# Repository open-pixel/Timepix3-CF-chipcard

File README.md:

# Timepix3-CF-chipcard
A compact Open Hardware chipboard for the Timepix3 chip from the [Medipix Collaboration](https://medipix.web.cern.ch/home) reusing the CompactFlash form factor.

Open the project file `TPX3_CF_chipcard.kicad_pro` in [KiCad V5.99 (*nightly version*)](https://www.kicad.org/download/) or the future version V6 once it is released. 

This project is licensed uner the CERN Open Hardware License: [CERN-OHL-P v2](LICENSE)

#### TODO:
- add more description and images
- 3D custom model files for the card enclosure and KiCad renderings
- update schematic with part order numbers

Author:
[Oliver Keller](https://www.github.com/ozel) (CERN/University of Geneva) 2021

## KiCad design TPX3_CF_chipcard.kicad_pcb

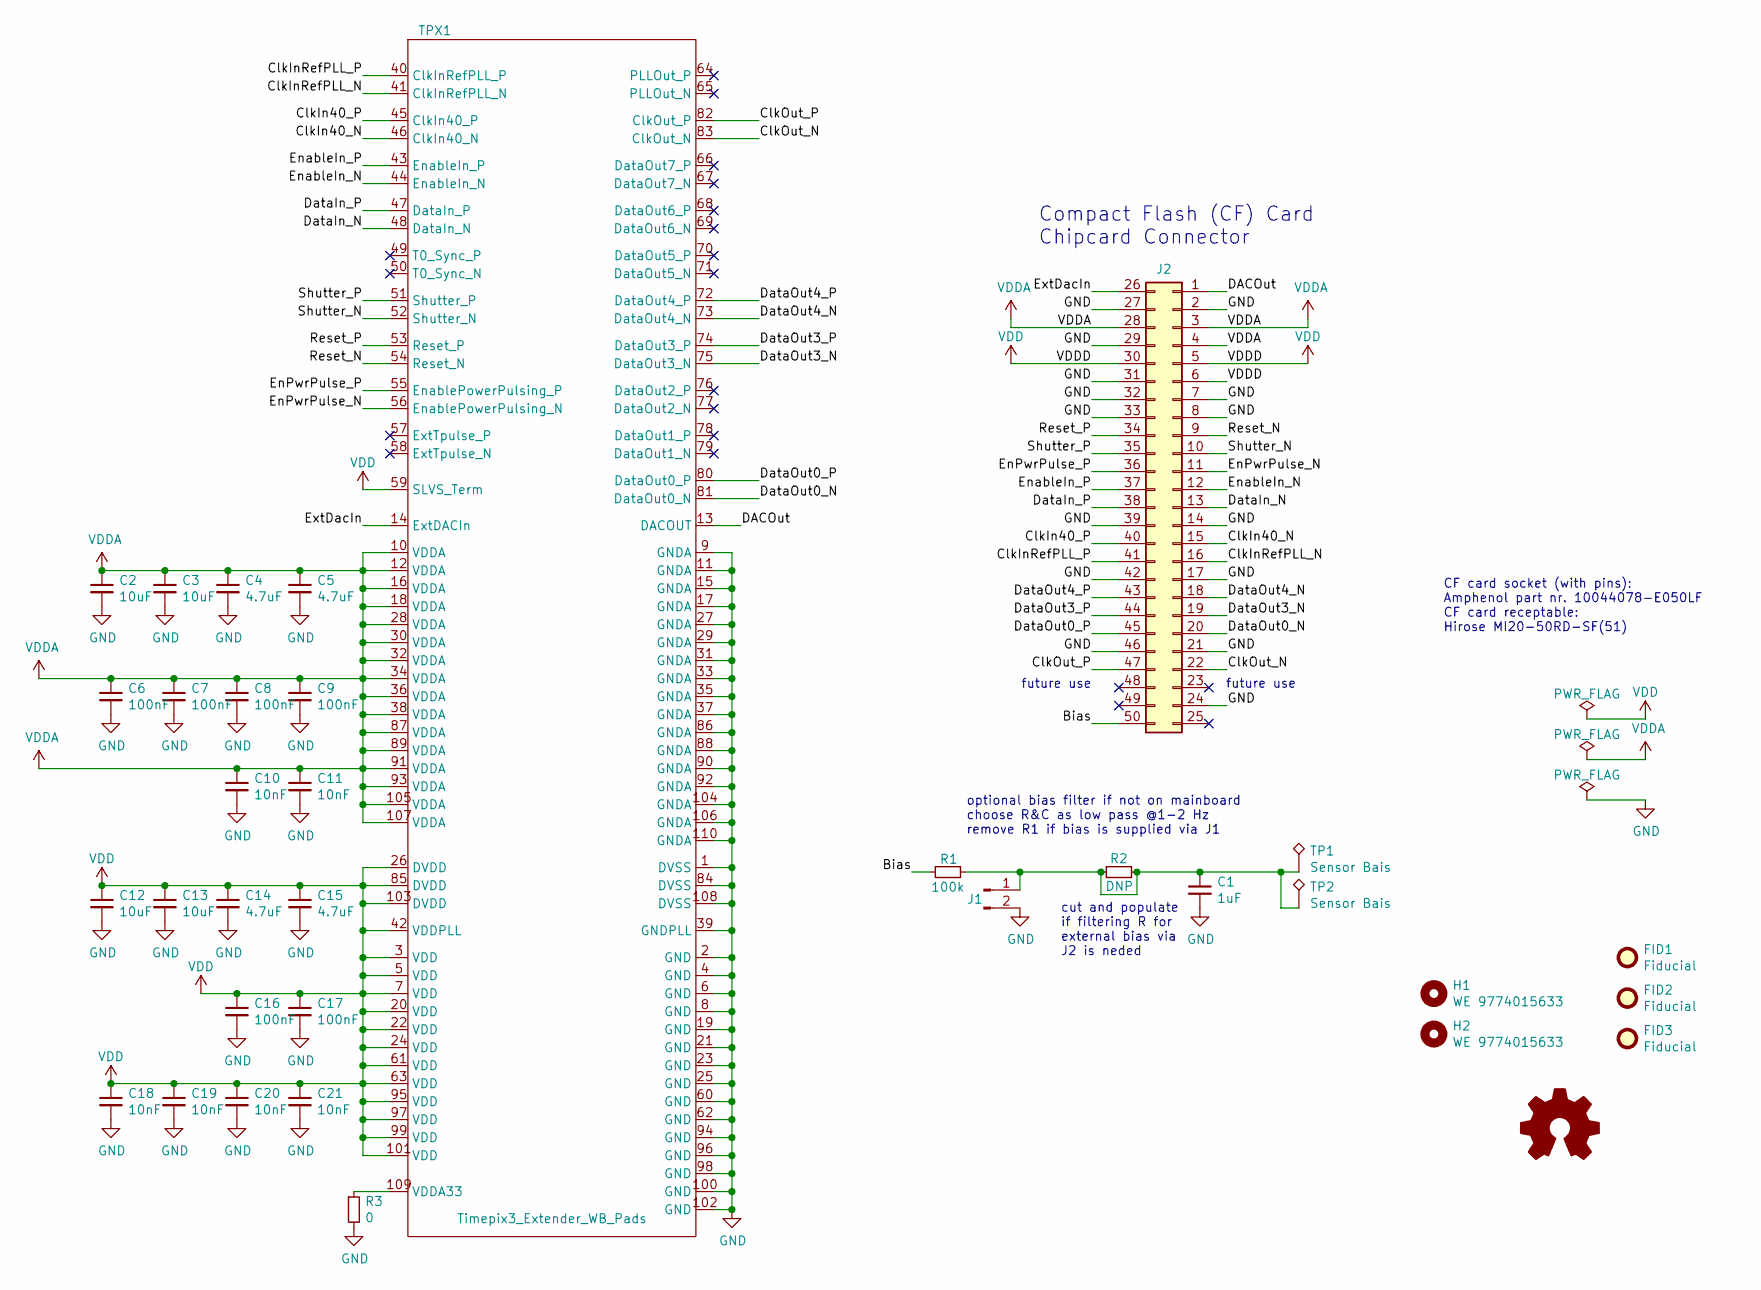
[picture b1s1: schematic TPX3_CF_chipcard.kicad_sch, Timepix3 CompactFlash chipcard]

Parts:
C1: 1uF; C_0805_2012Metric
C2, C3, C12, C13: 10uF; C_1206_3216Metric
C4, C5, C14, C15: 4.7uF; C_0805_2012Metric
C6, C7, C8, C9, C16, C17: 100nF; C_0402_1005Metric
C10, C11, C18, C19, C20, C21: 10nF; C_0402_1005Metric
FID1, FID2, FID3: Fiducial; Fiducial_0.75mm_Mask1.5mm
H1, H2: WE 9774015633; MountingHole_2.1mm
J1: Conn_01x02_Male; PinHeader_1x02_P2.54mm_Vertical
J2: MI20-50RD-SF(51); CF-Card_Hirose_MI20-50RD-SF(51)
LOGO1: Logo_Open_Hardware_Small; OSHW-Symbol_6.7x6mm_Copper
R1: 100k; R_0603_1608Metric
R2: DNP; R_0603_1608Metric
R3: 0; R_0603_1608Metric
TP1, TP2: Sensor Bais; TestPoint_Pad_2.0x2.0mm
TPX1: Timepix3_Extender_WB_Pads; Timepix3_lowcostWBpads

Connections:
/Bias: J2.50, R1.2
/ClkIn40_N: J2.15, TPX1.46 (ClkIn40_N)
/ClkIn40_P: J2.40, TPX1.45 (ClkIn40_P)
/ClkInRefPLL_N: J2.16, TPX1.41 (ClkInRefPLL_N)
/ClkInRefPLL_P: J2.41, TPX1.40 (ClkInRefPLL_P)
/ClkOut_N: J2.22, TPX1.83 (ClkOut_N)
/ClkOut_P: J2.47, TPX1.82 (ClkOut_P)
/DACOut: J2.1, TPX1.13 (DACOUT)
/DataIn_N: J2.13, TPX1.48 (DataIn_N)
/DataIn_P: J2.38, TPX1.47 (DataIn_P)
/DataOut0_N: J2.20, TPX1.81 (DataOut0_N)
/DataOut0_P: J2.45, TPX1.80 (DataOut0_P)
/DataOut3_N: J2.19, TPX1.75 (DataOut3_N)
/DataOut3_P: J2.44, TPX1.74 (DataOut3_P)
/DataOut4_N: J2.18, TPX1.73 (DataOut4_N)
/DataOut4_P: J2.43, TPX1.72 (DataOut4_P)
/EnPwrPulse_N: J2.11, TPX1.56 (EnablePowerPulsing_N)
/EnPwrPulse_P: J2.36, TPX1.55 (EnablePowerPulsing_P)
/EnableIn_N: J2.12, TPX1.44 (EnableIn_N)
/EnableIn_P: J2.37, TPX1.43 (EnableIn_P)
/ExtDacIn: J2.26, TPX1.14 (ExtDACIn)
/Reset_N: J2.9, TPX1.54 (Reset_N)
/Reset_P: J2.34, TPX1.53 (Reset_P)
/Shutter_N: J2.10, TPX1.52 (Shutter_N)
/Shutter_P: J2.35, TPX1.51 (Shutter_P)
GND: C1.2, C2.2, C3.2, C4.2, C5.2, C6.2, C7.2, C8.2, C9.2, C10.2, C11.2, C12.2, C13.2, C14.2, C15.2, C16.2, C17.2, C18.2, C19.2, C20.2, C21.2, J1.2, J2.2, J2.7, J2.8, J2.14, J2.17, J2.21, J2.24, J2.27, J2.29, J2.31, J2.32, J2.33, J2.39, J2.42, J2.46, R3.2, TPX1.1 (DVSS), TPX1.2 (GND), TPX1.4 (GND), TPX1.6 (GND), TPX1.8 (GND), TPX1.9 (GNDA), TPX1.11 (GNDA), TPX1.15 (GNDA), TPX1.17 (GNDA), TPX1.19 (GND), TPX1.21 (GND), TPX1.23 (GND), TPX1.25 (GND), TPX1.27 (GNDA), TPX1.29 (GNDA), TPX1.31 (GNDA), TPX1.33 (GNDA), TPX1.35 (GNDA), TPX1.37 (GNDA), TPX1.39 (GNDPLL), TPX1.60 (GND), TPX1.62 (GND), TPX1.84 (DVSS), TPX1.86 (GNDA), TPX1.88 (GNDA), TPX1.90 (GNDA), TPX1.92 (GNDA), TPX1.94 (GND), TPX1.96 (GND), TPX1.98 (GND), TPX1.100 (GND), TPX1.102 (GND), TPX1.104 (GNDA), TPX1.106 (GNDA), TPX1.108 (DVSS), TPX1.110 (GNDA)
unnamed: C1.1, J1.1, R1.1, R2.1, R2.2, TP1.1, TP2.1
unnamed: R3.1, TPX1.109 (VDDA33)
VDD: C12.1, C13.1, C14.1, C15.1, C16.1, C17.1, C18.1, C19.1, C20.1, C21.1, J2.5, J2.6, J2.30, TPX1.3 (VDD), TPX1.5 (VDD), TPX1.7 (VDD), TPX1.20 (VDD), TPX1.22 (VDD), TPX1.24 (VDD), TPX1.26 (DVDD), TPX1.42 (VDDPLL), TPX1.59 (SLVS_Term), TPX1.61 (VDD), TPX1.63 (VDD), TPX1.85 (DVDD), TPX1.95 (VDD), TPX1.97 (VDD), TPX1.99 (VDD), TPX1.101 (VDD), TPX1.103 (DVDD)
VDDA: C2.1, C3.1, C4.1, C5.1, C6.1, C7.1, C8.1, C9.1, C10.1, C11.1, J2.3, J2.4, J2.28, TPX1.10 (VDDA), TPX1.12 (VDDA), TPX1.16 (VDDA), TPX1.18 (VDDA), TPX1.28 (VDDA), TPX1.30 (VDDA), TPX1.32 (VDDA), TPX1.34 (VDDA), TPX1.36 (VDDA), TPX1.38 (VDDA), TPX1.87 (VDDA), TPX1.89 (VDDA), TPX1.91 (VDDA), TPX1.93 (VDDA), TPX1.105 (VDDA), TPX1.107 (VDDA)

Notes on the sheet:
optional bias filter if not on mainboard choose R&C as low pass @1-2 Hz remove R1 if bias is supplied via J1
Compact Flash (CF) Card Chipcard Connector
cut and populate if filtering R for external bias via J2 is neded
future use
CF card socket (with pins): Amphenol part nr. 10044078-E050LF CF card receptable: Hirose MI20-50RD-SF(51)

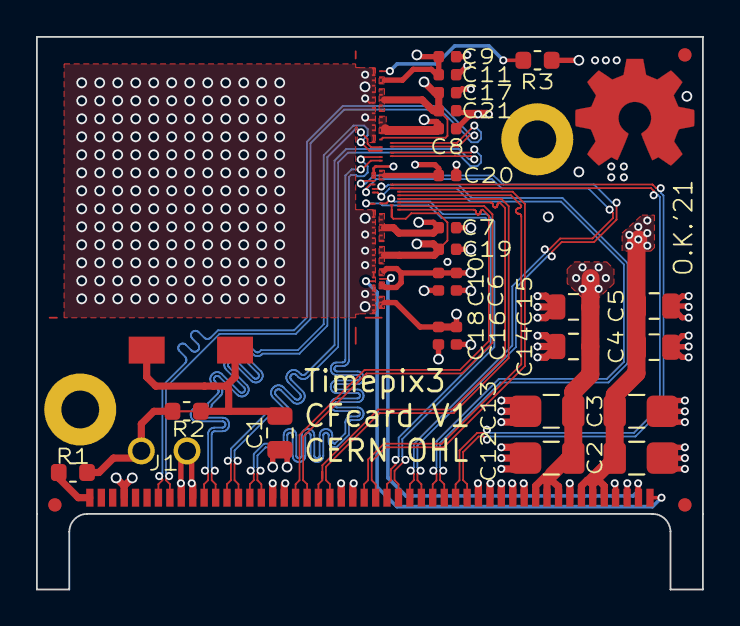
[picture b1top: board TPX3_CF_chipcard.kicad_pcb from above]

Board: 4 copper layers, 37.0 x 30.7 mm, 35 parts (0 on the bottom side), 30 nets.

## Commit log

2021-05-19 initial release
